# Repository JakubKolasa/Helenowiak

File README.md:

# Helenowiak
Projekt zakłada stworzenie robota od podstaw. Logika robota będzie oparta na mikrokontrolerze STM32. Zostanie on umieszczony na zaprojektowanej w programie KiCad płytce PCB. Model robota został zaprojektowany w programie AutoCAD Inventor.  Do detekcji przeciwnika wykorzystane zostaną czujniki zbliżeniowe działające w zakresie podczerwieni. W celu zastosowania bardziej skomplikowanych algorytmów walki i umożliwienia swobodnego poruszania się po dojo, robot zostanie wyposażony w czujniki odbiciowe mające na celu wykryć krawędzie areny, oraz enkodery umożliwiające dokładny pomiar przebytej odległości. Robot będzie komunikował się z komputerem poprzez moduł bluetooth dzięki czemu będzie można sterować nim w sposób zdalny przy pomocy odpowiednich komend.

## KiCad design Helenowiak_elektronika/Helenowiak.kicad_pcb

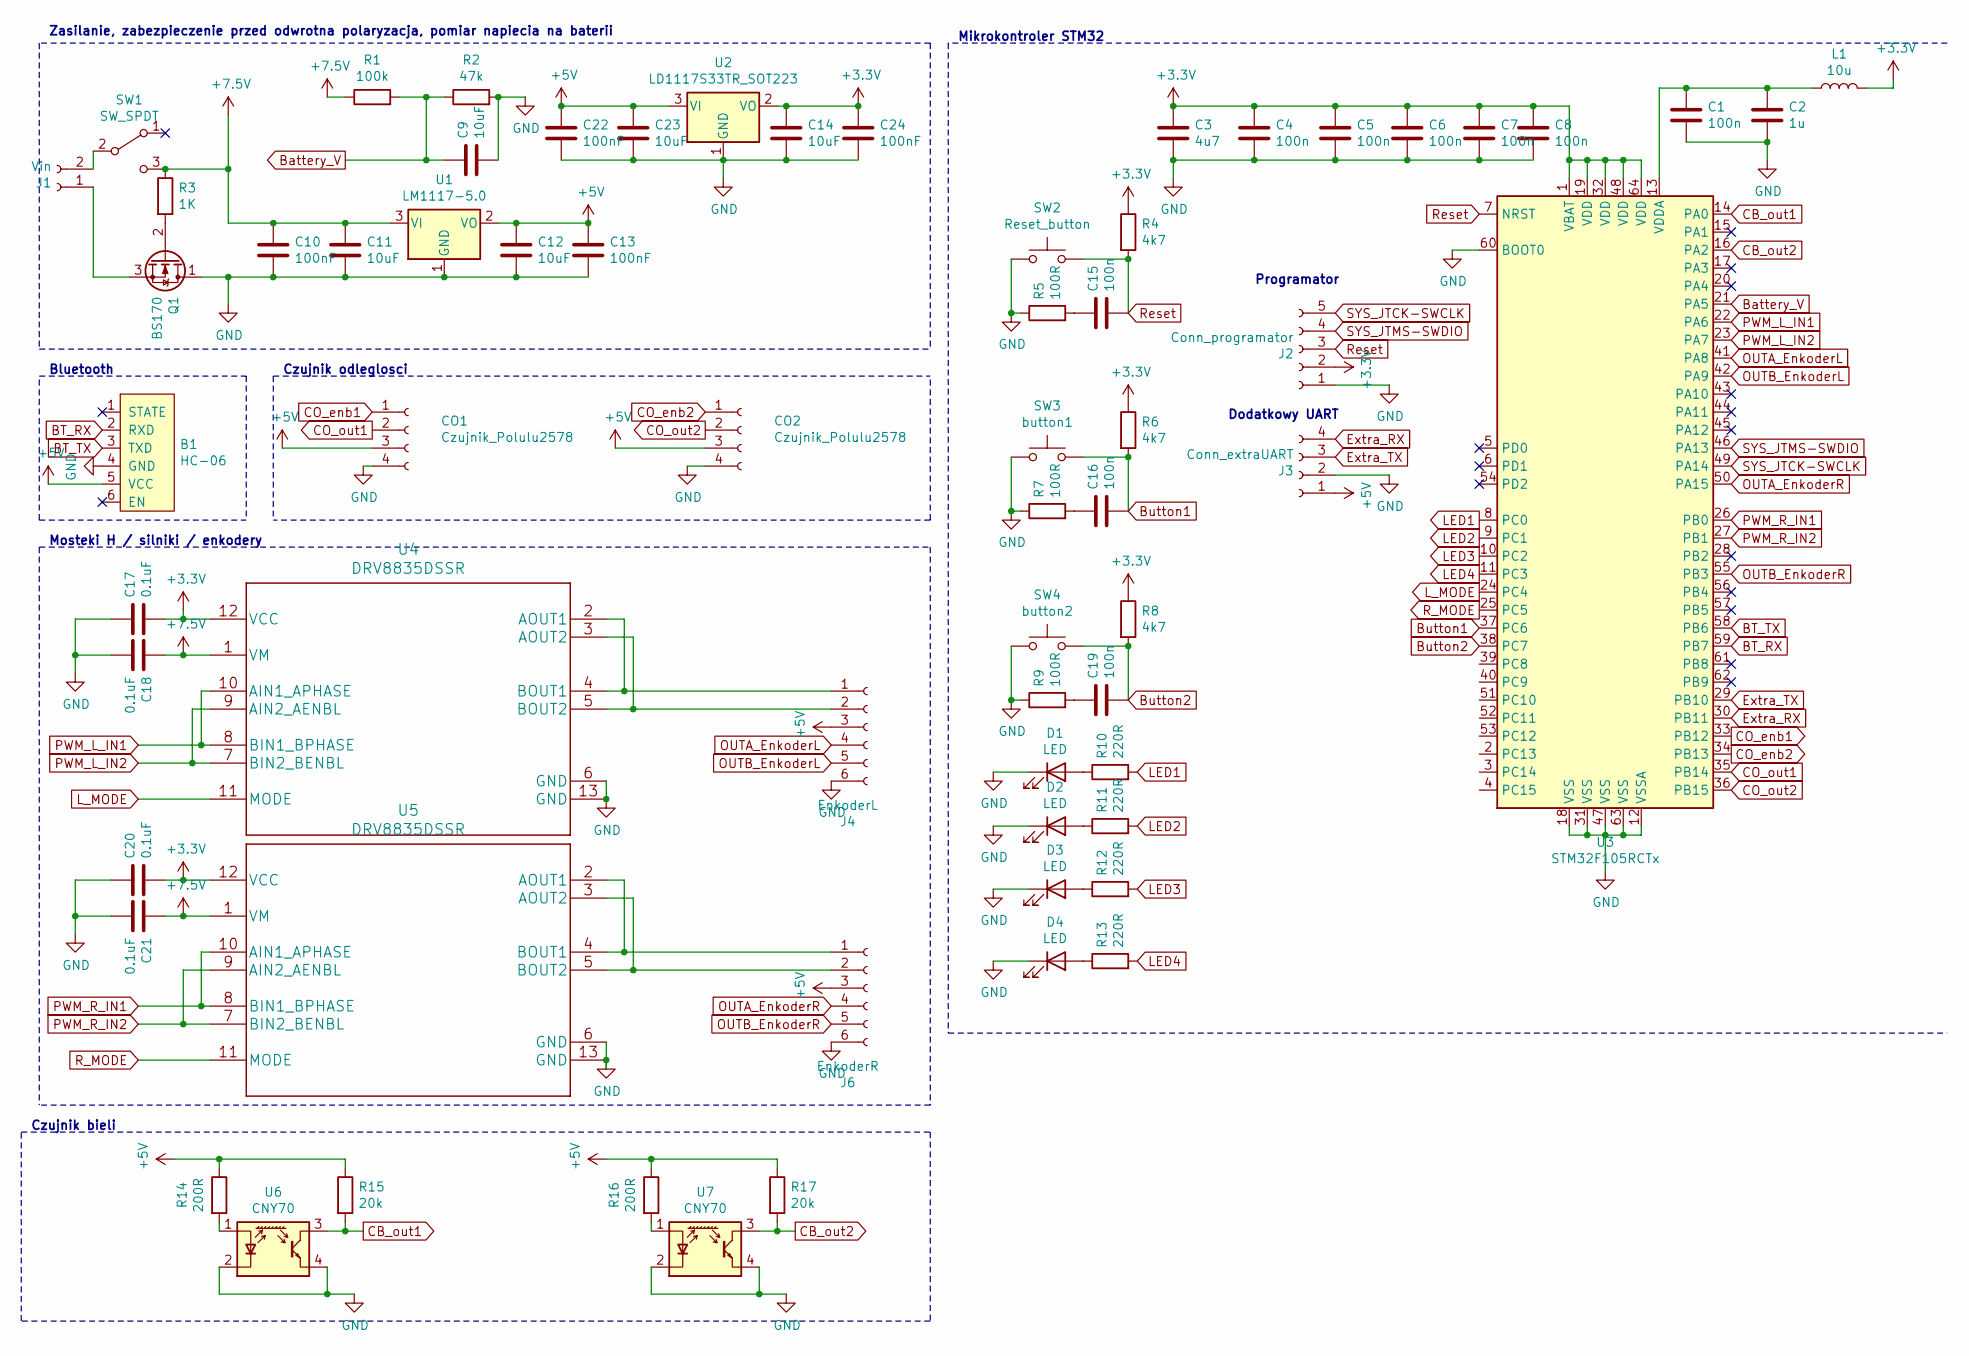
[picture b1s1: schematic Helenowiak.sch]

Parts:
B1: HC-06; PinSocket_1x06_P2.54mm_Vertical
C1, C4, C5, C6, C7, C8, C15, C16, C19: 100n; C_0603
C2: 1u; C_0603
C3: 4u7; C_0603
C9, C11, C12, C14, C23: 10uF; C_0603
C10, C13, C22, C24: 100nF; C_0603
C17, C18, C20, C21: 0.1uF; C_0603
CO1, CO2: Czujnik_Polulu2578; PinSocket_1x04_P2.54mm_Vertical
D1, D2, D3, D4: LED; LED_0603_1608Metric
J1: Vin; PinSocket_1x02_P2.54mm_Vertical
J2: Conn_programator; PinSocket_1x05_P2.54mm_Vertical
J3: Conn_extraUART; PinSocket_1x04_P2.54mm_Vertical
J4: EnkoderL; PinSocket_1x06_P2.54mm_Vertical
J6: EnkoderR; PinSocket_1x06_P2.54mm_Vertical
L1: 10u; L_0603
Q1: BS170; TO-92_Inline
R1: 100k; R_0603_1608Metric
R2: 47k; R_0603_1608Metric
R3: 1K; R_0603_1608Metric
R4, R6, R8: 4k7; R_0603_1608Metric
R5, R7, R9: 100R; R_0603_1608Metric
R10, R11, R12, R13: 220R; R_0603_1608Metric
R14, R16: 200R; R_0603_1608Metric
R15, R17: 20k; R_0603_1608Metric
SW1: SW_SPDT; PinSocket_1x03_P2.54mm_Vertical
SW2: Reset_button; button_mono
SW3: button1; button_mono
SW4: button2; button_mono
U1: LM1117-5.0; TO-220-3_Vertical
U2: LD1117S33TR_SOT223; SOT-223-3_TabPin2
U3: STM32F105RCTx; LQFP-64_10x10mm_P0.5mm
U4: DRV8835DSSR; WSON-12-1EP_3x2mm_Pitch0.5mm
U5: DRV8835DSSR; WSON-12-1EP_3x2mm_P0.5mm_EP1x2.65
U6, U7: CNY70; Vishay_CNY70

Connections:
+3V3: C3.1, C4.1, C5.1, C6.1, C7.1, C8.1, C14.1, C17.2, C20.2, C24.1, J2.2, L1.2, R4.1, R6.1, R8.1, U2.2 (VO), U3.1 (VBAT), U3.19 (VDD), U3.32 (VDD), U3.48 (VDD), U3.64 (VDD), U4.12 (VCC), U5.12 (VCC)
+5V: B1.5 (VCC), C12.1, C13.1, C22.1, C23.1, CO1.3, CO2.3, J3.1, J4.3, J6.3, R14.1, R15.1, R16.1, R17.1, U1.2 (VO), U2.3 (VI)
+7.5V: C10.1, C11.1, C18.1, C21.1, R1.1, R3.1, SW1.3 (C), U1.3 (VI), U4.1 (VM), U5.1 (VM)
BT_RX: B1.2 (RXD), U3.59 (PB7)
BT_TX: B1.3 (TXD), U3.58 (PB6)
Battery_V: C9.1, R1.2, R2.1, U3.21 (PA5)
Button1: C16.2, R6.2, SW3.2, U3.37 (PC6)
Button2: C19.2, R8.2, SW4.2, U3.38 (PC7)
CB_out1: R15.2, U3.14 (PA0), U6.3 (C)
CB_out2: R17.2, U3.16 (PA2), U7.3 (C)
CO_enb1: CO1.1, U3.33 (PB12)
CO_enb2: CO2.1, U3.34 (PB13)
CO_out1: CO1.2, U3.35 (PB14)
CO_out2: CO2.2, U3.36 (PB15)
Extra_RX: J3.4, U3.30 (PB11)
Extra_TX: J3.3, U3.29 (PB10)
GND: B1.4 (GND), C1.2, C2.2, C3.2, C4.2, C5.2, C6.2, C7.2, C8.2, C9.2, C10.2, C11.2, C12.2, C13.2, C14.2, C17.1, C18.2, C20.1, C21.2, C22.2, C23.2, C24.2, CO1.4, CO2.4, D1.1 (K), D2.1 (K), D3.1 (K), D4.1 (K), J2.1, J3.2, J4.6, J6.6, Q1.1 (D), R2.2, R5.1, R7.1, R9.1, SW2.1, SW3.1, SW4.1, U1.1 (GND), U2.1 (GND), U3.12 (VSSA), U3.18 (VSS), U3.31 (VSS), U3.47 (VSS), U3.60 (BOOT0), U3.63 (VSS), U4.6 (GND), U4.13 (GND), U5.6 (GND), U5.13 (GND), U6.2 (K), U6.4 (E), U7.2 (K), U7.4 (E)
LED1: R10.2, U3.8 (PC0)
LED2: R11.2, U3.9 (PC1)
LED3: R12.2, U3.10 (PC2)
LED4: R13.2, U3.11 (PC3)
L_MODE: U3.24 (PC4), U4.11 (MODE)
unnamed: C1.1, C2.1, L1.1, U3.13 (VDDA)
unnamed: C15.1, R5.2
unnamed: C16.1, R7.2
unnamed: C19.1, R9.2
unnamed: D1.2 (A), R10.1
unnamed: D2.2 (A), R11.1
unnamed: D3.2 (A), R12.1
unnamed: D4.2 (A), R13.1
unnamed: J1.1, Q1.3 (S)
unnamed: J1.2, SW1.2 (B)
unnamed: J4.1, U4.2 (AOUT1), U4.4 (BOUT1)
unnamed: J4.2, U4.3 (AOUT2), U4.5 (BOUT2)
unnamed: J6.1, U5.2 (AOUT1), U5.4 (BOUT1)
unnamed: J6.2, U5.3 (AOUT2), U5.5 (BOUT2)
unnamed: Q1.2 (G), R3.2
unnamed: R14.2, U6.1 (A)
unnamed: R16.2, U7.1 (A)
OUTA_EnkoderL: J4.4, U3.41 (PA8)
OUTA_EnkoderR: J6.4, U3.50 (PA15)
OUTB_EnkoderL: J4.5, U3.42 (PA9)
OUTB_EnkoderR: J6.5, U3.55 (PB3)
PWM_L_IN1: U3.22 (PA6), U4.8 (BIN1_BPHASE), U4.10 (AIN1_APHASE)
PWM_L_IN2: U3.23 (PA7), U4.7 (BIN2_BENBL), U4.9 (AIN2_AENBL)
PWM_R_IN1: U3.26 (PB0), U5.8 (BIN1_BPHASE), U5.10 (AIN1_APHASE)
PWM_R_IN2: U3.27 (PB1), U5.7 (BIN2_BENBL), U5.9 (AIN2_AENBL)
R_MODE: U3.25 (PC5), U5.11 (MODE)
Reset: C15.2, J2.3, R4.2, SW2.2, U3.7 (NRST)
SYS_JTCK-SWCLK: J2.5, U3.49 (PA14)
SYS_JTMS-SWDIO: J2.4, U3.46 (PA13)

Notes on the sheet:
Czujnik odleglosci
Czujnik bieli
Bluetooth
Mosteki H / silniki / enkodery
Mikrokontroler STM32
Zasilanie, zabezpieczenie przed odwrotna polaryzacja, pomiar napiecia na baterii
Programator
Dodatkowy UART

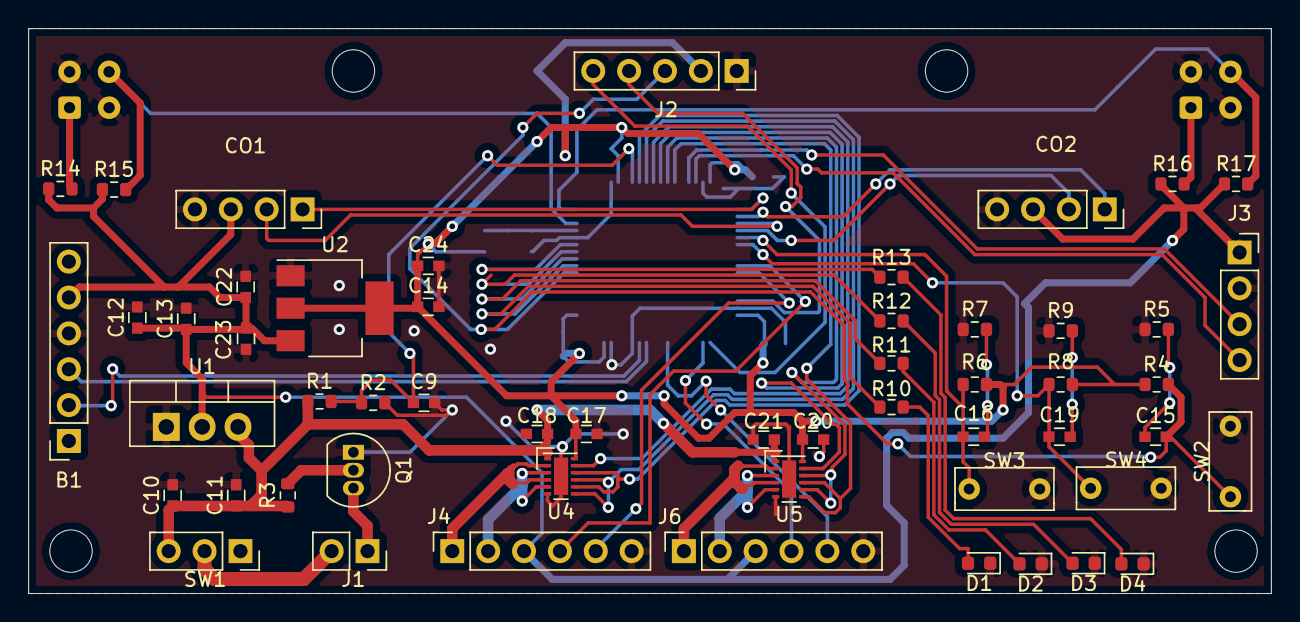
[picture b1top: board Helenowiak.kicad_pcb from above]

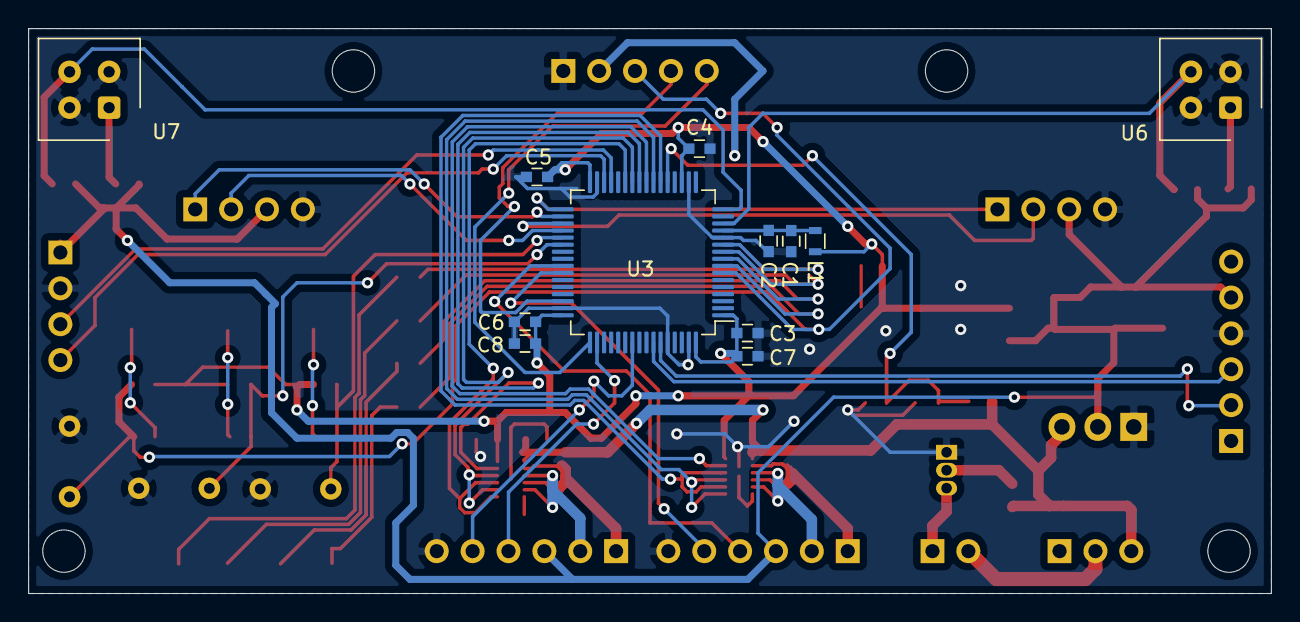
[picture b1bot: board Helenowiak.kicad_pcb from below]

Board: 2 copper layers, 88.0 x 40.0 mm, 66 parts (12 on the bottom side), 51 nets.

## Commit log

2021-03-17 Pierwszy commit, poczatki projektowania elektroniki
2021-03-18 Wszystko oprocz stm32
2021-04-03 Mechanika prawie gotowa, elektronika brak stm32
2021-04-15 New stm32
2021-04-20 New pinout
2021-04-21 Finished eschema
2021-04-25 Etap II
2021-04-26 Dodana prezentacja algorytmu
2021-04-26 Usunieto txt z notatkami
2021-05-02 PCB 75%
2021-05-04 Przed wylaniem masy
2021-05-04 PCB zamowione
